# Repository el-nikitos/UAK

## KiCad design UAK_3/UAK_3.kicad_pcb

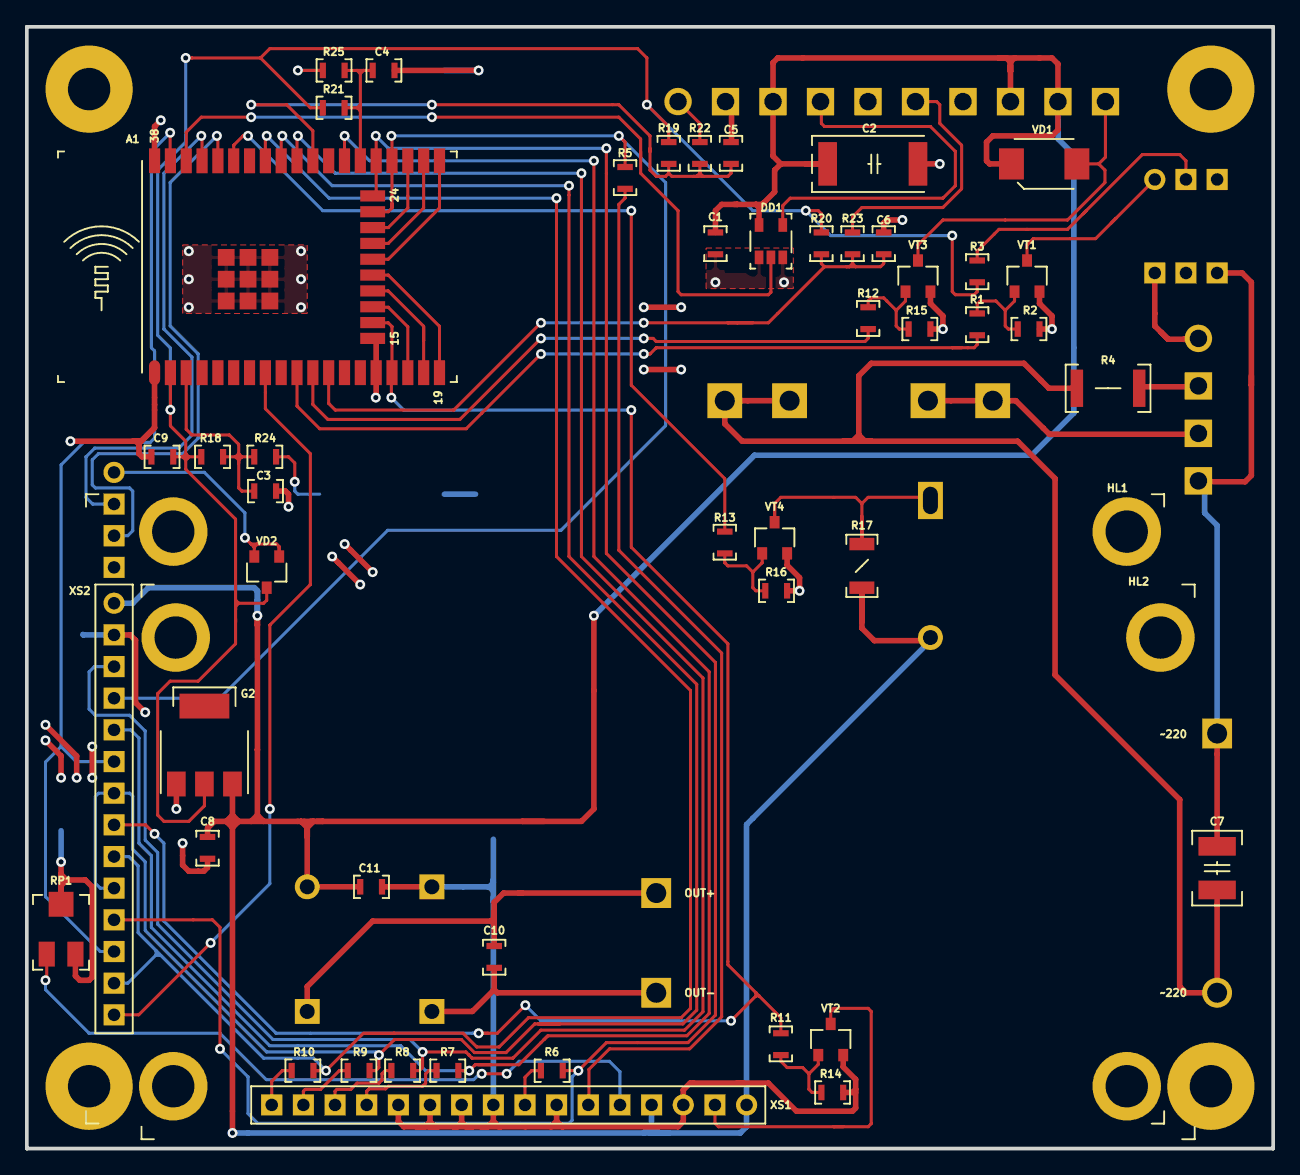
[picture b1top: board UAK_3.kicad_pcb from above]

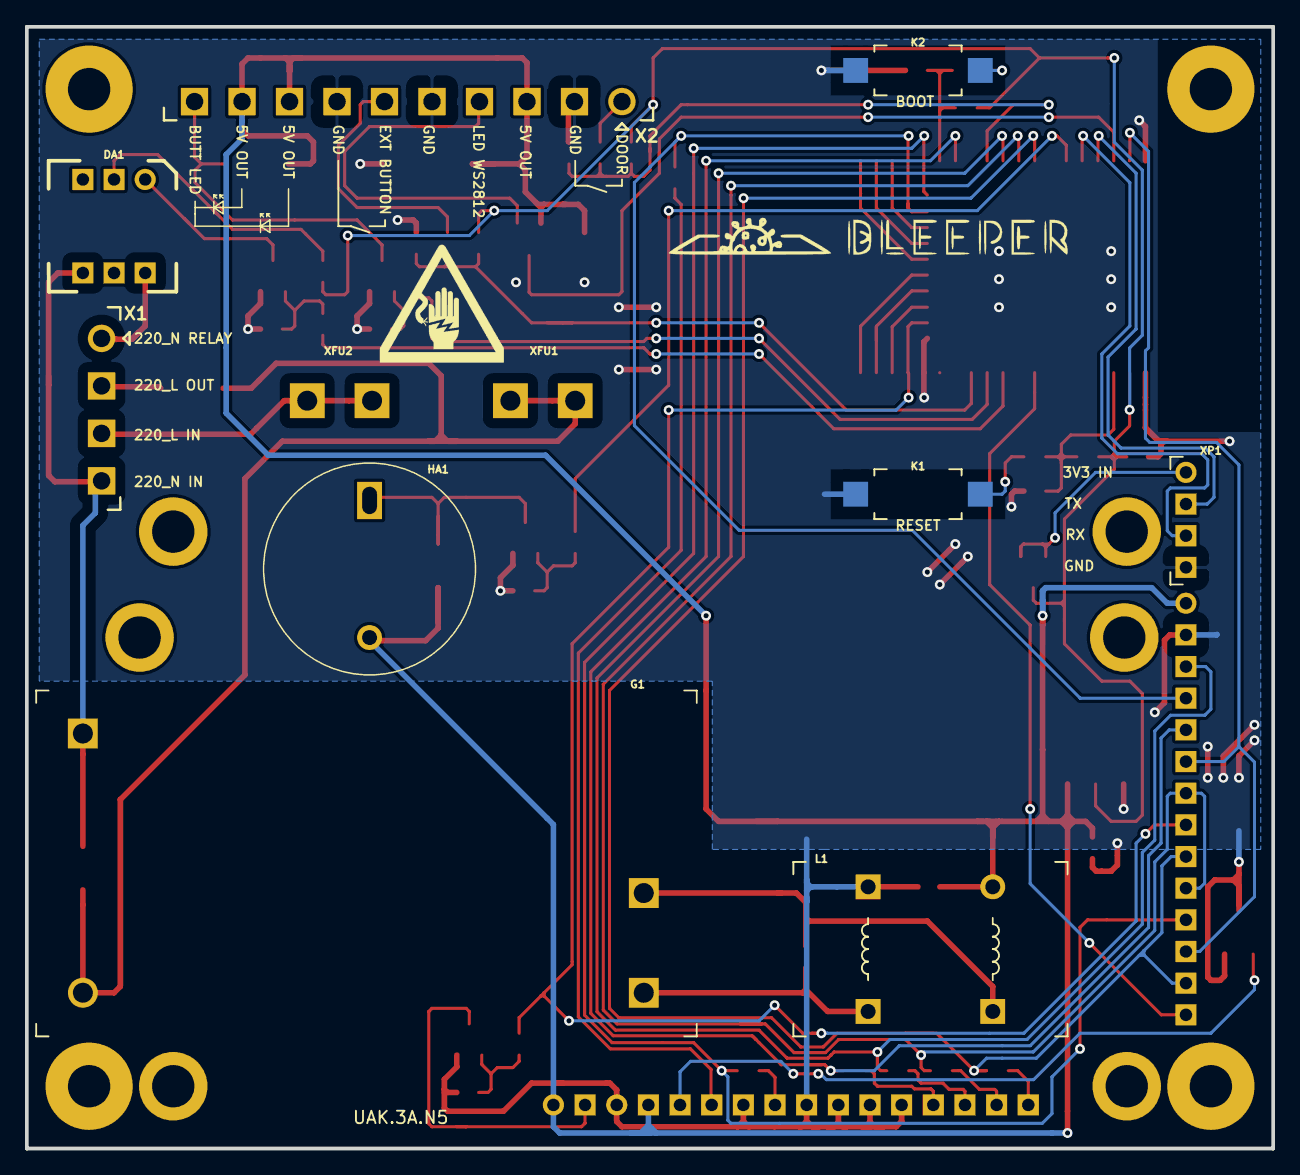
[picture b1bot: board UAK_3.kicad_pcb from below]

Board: 2 copper layers, 100.0 x 90.0 mm, 65 parts (13 on the bottom side), 51 nets.

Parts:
A1: модуль_esp32_wrover_OR_wroom32_SMD; ESP32_WROVER_or_WROOM32_pnp
C1, C3, C4, C5, C6, C8, C9, C10, C11: Конденсатор_керамический; Конденсатор_SMD_0603_pnp
C2: Конденсатор_К53-56А-32В-22_мкФ+-10проц.; Конденсатор_тантал_SMD_m7343_pnp
C7: Конденсатор_керамический; Конденсатор_SMD_1210_pnp
D1: LOGO; danger_220
D2: LOGO; bleeper_4x33
DA1: МОП-реле_КР293КП1Б; DIP6
DD1: Повторитель_M74VHC1GT125; SOT-23-5_pnp
G1: AC-DC-преобразователь_IRM-15-5; AC-DC_IRM-20-12
G2: стабилизатор_нерегулируемый_LM1117GS-3.3; Транзистор_NPN_SOT223_pnp
HA1: Излучатель_HPA17F; Зуммер_HPA17F
HL1: TFT-дисплей_ST7735_ILI9341; TFT_2.8_INCH
HL2: Жидкокристалический_индикатор_MT-16S2H-2KLW; ЖК_MT-16S2H_2DRL
K1, K2: Кнопка_FSMSM
L1: Дроссель_B82731-T2132-A20_2х6.8мГн_1.3А_250В; Дроссель_B82731
R1, R2, R3, R5, R6, R7, R8, R9, R10, R11, R12, R13, R14, R15, R16, R18, R19, R20, R21, R22, R23, R24, R25: Резистор_0,065Вт; Резистор_SMD_0603_0,065_Вт_pnp
R4: Резистор_0,5Вт; Резистор_SMD_2010-0,5_Вт_pnp
R17: Резистор_0,25Вт; Резистор_SMD_1206-0,25_Вт_pnp
RP1: Резистор_подстроечный_PVA3A103; резистор_подстроечный_3314J-1_pnp
VD1: Диод_шоттки_SK16; Диод_SMB_pnp
VD2: Набор_диодов_BAR43CFILM; Корпус_КТ-46_pnp
VT1, VT2, VT3, VT4: Транзистор_полевой_N-канальный_IRLML6344TR; Корпус_КТ-46_pnp
X1: Клеммник_х4; Клеммник_х4_шаг3,81_15EDGRC
X2: Клеммник_х10; Клеммник_х10_шаг3,81_15EDGRC
X3, X4, X5, X6: Крепежное_отверстие_М3; Крепежное_Отверстие_под_М3
XFU1, XFU2: Держатель_предохранителя_KLS5-266; Держатель_5х20
XP1: Вилка_WF-4R; Вилка_СНП389-4ВП32-1-1

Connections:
/3V3: A1.2, C9.1, G2.2, R3.2, R18.1, R19.1, R20.1, R21.1, VD2.3
/5V: C1.1, C2.1, C8.1, C11.1, DD1.5, G2.3, HA1.1, HL1.1, HL2.2, HL2.15, L1.1, R17.1, VD1.1, X2.3, X2.8, X2.9
/220_L: X1.3, XFU2.1
/220_L_FU: C7.1, G1.L, R4.1, XFU1.1
/220_L_OUT: R4.2, X1.2
/220_N: C7.2, DA1.4, G1.N, X1.4
/220_N_OUT: DA1.6, X1.1
/BOOT_SEL: A1.25, C4.1, R21.2, R25.2
/BOOT_UART_RX: A1.34, XP1.3
/BOOT_UART_TX: A1.35, XP1.2
/BUTT_1: R23.1, X2.6
/BUZZER: A1.33, R13.2
/DOOR_1: R22.1, X2.1
/DOOR_SENSOR: A1.28, C5.2, R19.2, R22.2
/D_OUT_1: VD1.2, VT3.3, X2.10
/EN_RESET: A1.3, C3.1, R18.2, R24.2
/EXT_BUTTON: A1.12, C6.2, R20.2, R23.2
/GND: A1.1, A1.15, A1.38, A1.39, C1.2, C2.2, C3.2, C4.2, C5.1, C6.1, C8.2, C9.2, C11.2, DD1.1, DD1.3, G2.1, HL1.2, HL2.1, HL2.5, HL2.7, HL2.8, HL2.9, HL2.10, K1.1, K2.1, L1.3, R2.2, R14.2, R15.2, R16.2, RP1.2, RP1.3, VT1.2, VT2.2, VT3.2, VT4.2, X2.2, X2.5, X2.7, XP1.4
/LCD_A0: A1.23, HL1.4, R5.2
/LCD_DATA_4: A1.26, HL1.5, R7.2
/LCD_DATA_5: A1.29, HL1.3, R8.2
/LCD_DATA_6: A1.30, HL1.7, HL1.10, R9.2
/LCD_DATA_7: A1.31, HL1.9, HL1.13, R10.2
/LCD_E: A1.24, HL1.11, R6.2
/LCD_LED: A1.16, HL1.8, R11.2
/LED_OUT: DD1.4, X2.4
/LED_WS2812: A1.36, DD1.2
/MC_220_OUT: A1.10, R1.2
/MC_OUT_1: A1.11, R12.2
/MOSI: A1.37, HL1.6, HL1.12
/SUPPLY_POWER/5V_NOISE: C10.1, G1.+V, L1.6
/TOUCH_IRQ: A1.8, HL1.14
unnamed: C10.2, G1.-V, L1.4
unnamed: DA1.1, VT1.3
unnamed: DA1.2, R3.1
unnamed: HA1.2, R17.2, VT4.3
unnamed: HL2.3, RP1.1
unnamed: HL2.4, R5.1
unnamed: HL2.6, R6.1
unnamed: HL2.11, R7.1
unnamed: HL2.12, R8.1
unnamed: HL2.13, R9.1
unnamed: HL2.14, R10.1
unnamed: HL2.16, VT2.3
unnamed: K1.2, R24.1
unnamed: K2.2, R25.1
unnamed: R1.1, R2.1, VT1.1
unnamed: R11.1, R14.1, VT2.1
unnamed: R12.1, R15.1, VT3.1
unnamed: R13.1, R16.1, VT4.1
unnamed: VD2.1, VD2.2, XP1.1

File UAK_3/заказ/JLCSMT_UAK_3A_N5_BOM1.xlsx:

Comment | Designator | Footprint | LCSC Part #（optional） |  | new name
ESP32-WROOM-32E | A1 | SMD38,18x25.5 | C701341 | 0 | ESP32-WROOM-32E
100nF 50V | C1 | 0603_C | C14663 | 0 | 100nF 50V
100uF 10V | C2 | CASE-D_7343 | C313070 | 0 | 100uF 10V
100nF 50V | C3 | 0603_C | C14663 | 0 | 100nF 50V
100nF 50V | C4 | 0603_C | C14663 | 1 | ?
100nF 50V | C5 | 0603_C | C14663 | 1 | ?
100nF 50V | C6 | 0603_C | C14663 | 1 | ?
22nF 1kV | C7 | 1210_C | C304015 | 0 | 22nF 1kV
10uF 10V | C8 | 0603_C | C19702 | 0 | 10uF 10V
10uF 10V | C9 | 0603_C | C19702 | 1 | ?
10uF 10V | C10 | 0603_C | C19702 | 1 | ?
10uF 10V | C11 | 0603_C | C19702 | 1 | ?
M74VHC1GT125DT1G | DD1 | SOT-23-5 | C457671 | 0 | M74VHC1GT125DT1G
SC1117-3.3V | G2 | SOT-223 | C173386 | 0 | SC1117-3.3V
240Ω | R1 | 0603_R | C101310 | 0 | 240Ω
10kΩ | R2 | 0603_R | C510290 | 0 | 10kΩ
150Ω | R3 | 0603_R | C336847 | 0 | 150Ω
130Ω | R4 | 2010_R | C406994 | 0 | 130Ω
240Ω | R5 | 0603_R | C101310 | 0 | 240Ω
240Ω | R6 | 0603_R | C101310 | 1 | ?
240Ω | R7 | 0603_R | C101310 | 1 | ?
240Ω | R8 | 0603_R | C101310 | 1 | ?
240Ω | R9 | 0603_R | C101310 | 1 | ?
240Ω | R10 | 0603_R | C101310 | 1 | ?
240Ω | R11 | 0603_R | C101310 | 1 | ?
240Ω | R12 | 0603_R | C101310 | 1 | ?
240Ω | R13 | 0603_R | C101310 | 1 | ?
10kΩ | R14 | 0603_R | C510290 | 0 | 10kΩ
10kΩ | R15 | 0603_R | C510290 | 1 | ?
10kΩ | R16 | 0603_R | C510290 | 1 | ?
1kΩ | R17 | 1206_R | C830401 | 0 | 1kΩ
10kΩ | R18 | 0603_R | C510290 | 0 | 10kΩ
10kΩ | R19 | 0603_R | C510290 | 1 | ?
10kΩ | R20 | 0603_R | C510290 | 1 | ?
10kΩ | R21 | 0603_R | C510290 | 1 | ?
240Ω | R22 | 0603_R | C101310 | 0 | 240Ω
240Ω | R23 | 0603_R | C101310 | 1 | ?
240Ω | R24 | 0603_R | C101310 | 1 | ?
240Ω | R25 | 0603_R | C101310 | 1 | ?
10K Variable Resistors | RP1 | 3314J | C36376 | 0 | 10K Variable Resistors
MDD SS24B | VD1 | SMB(DO-214AA) | C35501 | 0 | MDD SS24B
BAT54CLT1G | VD2 | SOT-23-3 | C14308 | 0 | BAT54CLT1G
IRLML6344TR | VT1 | SOT-23-3 | C693370 | 0 | IRLML6344TR
IRLML6344TR | VT2 | SOT-23-3 | C693370 | 1 | ?
IRLML6344TR | VT3 | SOT-23-3 | C693370 | 1 | ?
IRLML6344TR | VT4 | SOT-23-3 | C693370 | 1 | ?

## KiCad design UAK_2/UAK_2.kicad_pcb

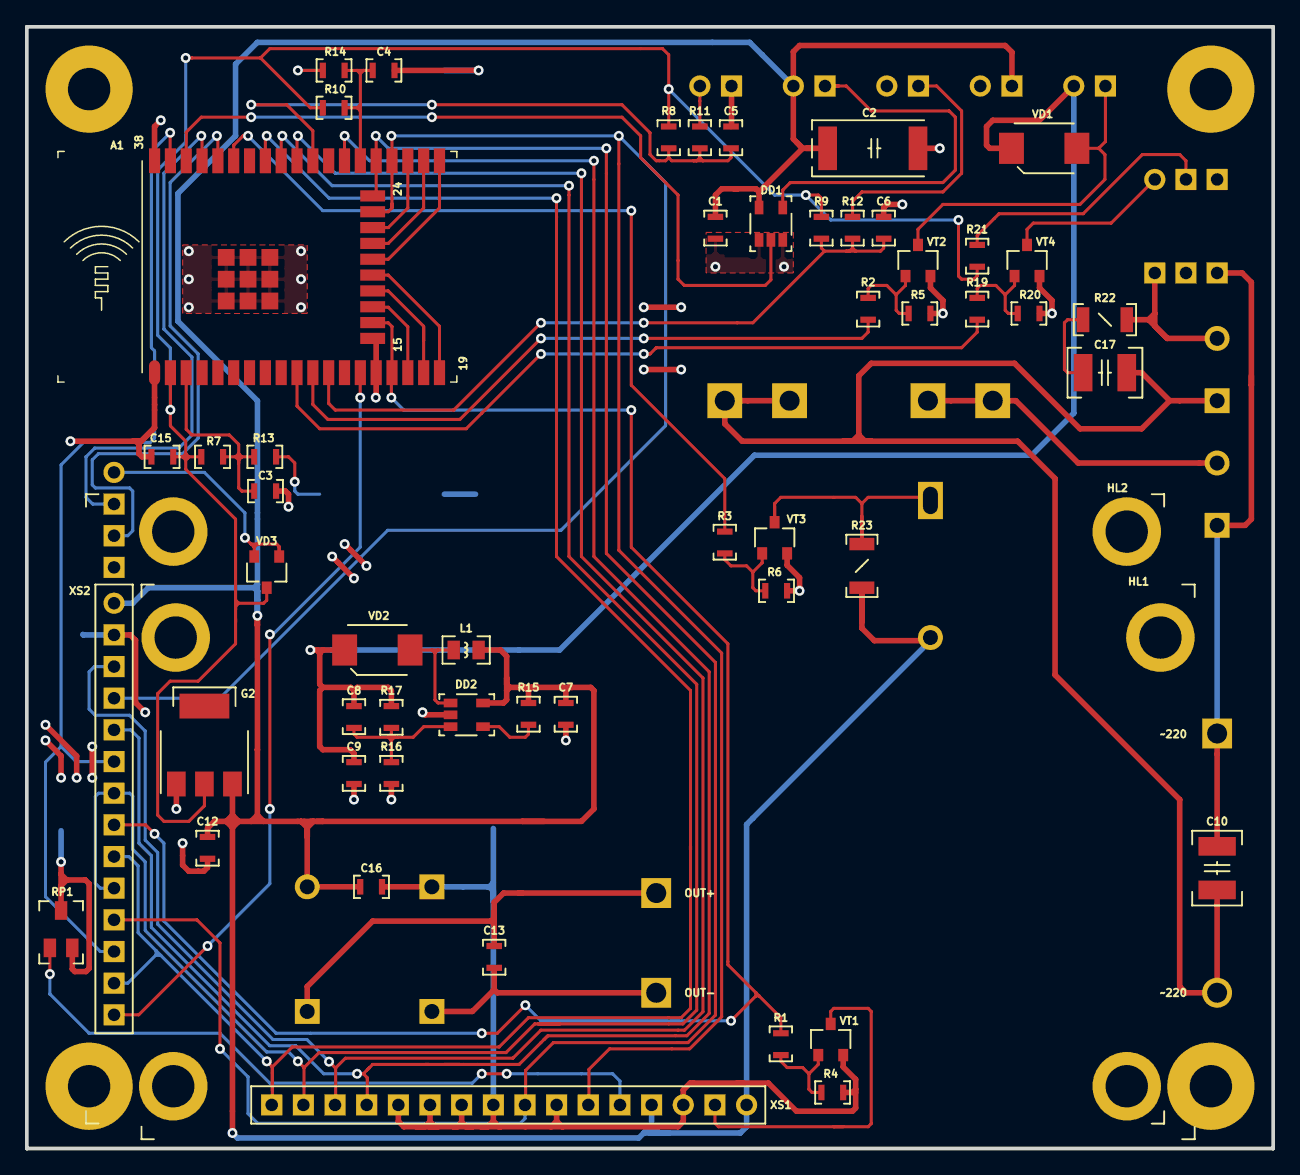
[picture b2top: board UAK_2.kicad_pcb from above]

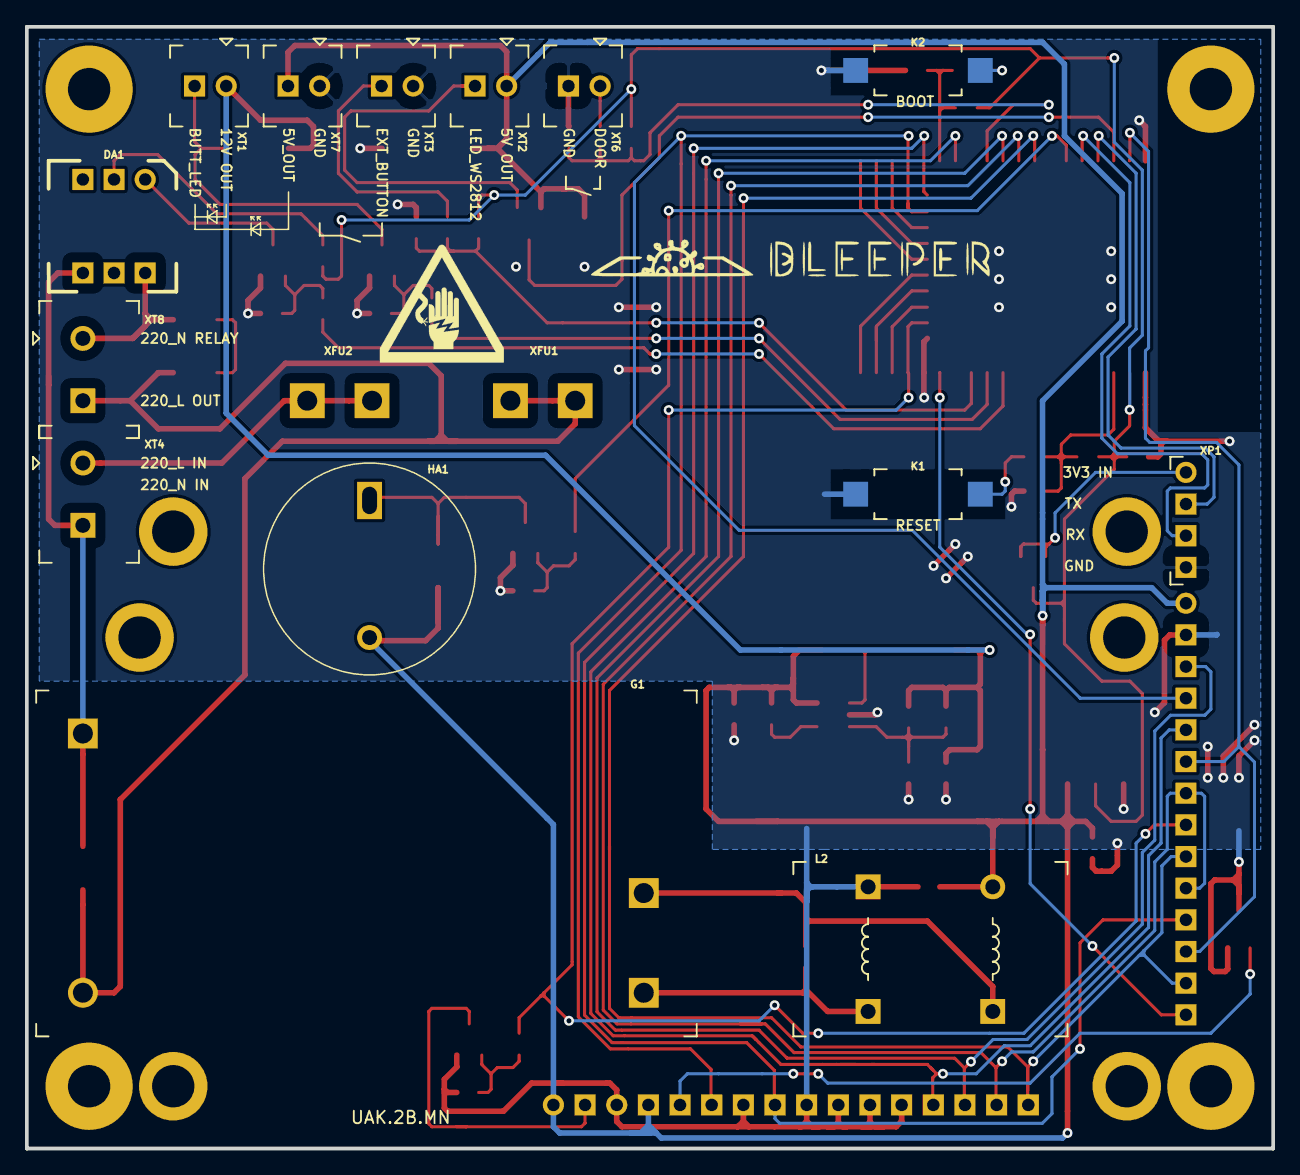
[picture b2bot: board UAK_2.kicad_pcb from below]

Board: 2 copper layers, 100.0 x 90.0 mm, 74 parts (18 on the bottom side), 49 nets.

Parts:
A1: модуль_esp32_wrover_OR_wroom32_SMD; ESP32_WROVER_or_WROOM32
C1, C3, C4, C5, C6, C7, C8, C9, C12, C13, C15, C16: Конденсатор_керамический; Конденсатор_SMD_0603
C2: Конденсатор_К53-56А-32В-22_мкФ+-10проц.; Конденсатор_тантал_SMD_m7343
C10, C17: Конденсатор_керамический; Конденсатор_SMD_1210
D1: LOGO; bleeper_4x33
D2: LOGO; danger_220
DA1: МОП-реле_КР293КП1Б; DIP6
DD1: Повторитель_M74VHC1GT125; Преобразователь_LM2703_SOT-23-5
DD2: Микросхема_DCDC_step_UP_LM2703; Преобразователь_LM2703_SOT-23-5
G1: AC-DC-преобразователь_IRM-15-5; AC-DC_IRM-20-12
G2: стабилизатор_нерегулируемый_LM1117GS-3.3; Транзистор_NPN_SOT223
HA1: Излучатель_HPA17F; Зуммер_HPA17F
HL1: Жидкокристалический_индикатор_MT-16S2H-2KLW; ЖК_MT-16S2H_2DRL
HL2: TFT-дисплей_ST7735_ILI9341; TFT_2.8_INCH
K1, K2: Кнопка_FSMSM
L1: Чип-индуктивность_10мкГн_0.2А_20проц.; Чип-индуктивность_SMD_0805
L2: Дроссель_B82731-T2132-A20_2х6.8мГн_1.3А_250В; Дроссель_B82731
R1, R2, R3, R4, R5, R6, R7, R8, R9, R10, R11, R12, R13, R14, R15, R16, R17, R19, R20, R21: Резистор_0,065Вт; Резистор_SMD_0603_0,065_Вт
R22, R23: Резистор_0,25Вт; Резистор_SMD_1206-0,25_Вт
RP1: Резистор_подстроечный_PVA3A103; резистор_подстроечный_PVZ3A334
VD1, VD2: Диод_шоттки_SK16; Диод_SMB
VD3: Набор_диодов_BAR43CFILM; Корпус_КТ-46
VT1, VT2, VT3, VT4: Транзистор_полевой_N-канальный_IRLML6344TR; Корпус_КТ-46
X1, X2, X3, X4: Крепежное_отверстие_М3; Крепежное_Отверстие_под_М3
XFU1, XFU2: Держатель_предохранителя_KLS5-266; Держатель_5х20
XP1: Вилка_WF-4R; Вилка_СНП389-4ВП32-1-1
XT1, XT2, XT3, XT6, XT7: Клеммник_х2_308-021-14; Клеммник_х2_шаг2.54
XT4, XT8: Клеммник_х2_KLS2-300-5.00-02P-2S; Клеммник_х2_шаг5

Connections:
/3V3: A1.2, C15.1, G2.2, R7.1, R8.1, R9.1, R10.1, R21.2, VD3.3
/5V: C1.1, C2.1, C7.1, C12.1, C16.1, DD1.5, DD2.5, G2.3, HA1.1, HL1.2, HL1.15, HL2.1, L1.2, L2.1, R15.1, R23.1, XT2.1, XT7.2
/12V: C8.2, C9.1, R17.1, VD1.2, VD2.2, XT1.1
/220_L: XFU2.1, XT4.1
/220_L_FU: C10.1, C17.2, G1.L, XFU1.1, XT8.2
/220_N: C10.2, DA1.4, G1.N, XT4.2
/220_N_OUT: DA1.6, R22.1, XT8.1
/BOOT_SEL: A1.25, C4.1, R10.2, R14.2
/BOOT_UART_RX: A1.34, XP1.3
/BOOT_UART_TX: A1.35, XP1.2
/BUTT_1: R12.1, XT3.2
/BUZZER: A1.33, R3.2
/DOOR_1: R11.1, XT6.1
/DOOR_SENSOR: A1.28, C5.2, R8.2, R11.2
/D_OUT_1: VD1.1, VT2.3, XT1.2
/EN_RESET: A1.3, C3.1, R7.2, R13.2
/EXT_BUTTON: A1.12, C6.2, R9.2, R12.2
/GND: A1.1, A1.15, A1.38, A1.39, C1.2, C2.2, C3.2, C4.2, C5.1, C6.1, C7.2, C9.2, C12.2, C15.2, C16.2, DD1.1, DD1.3, DD2.2, G2.1, HL1.1, HL1.5, HL1.7, HL1.8, HL1.9, HL1.10, HL2.2, K1.1, K2.1, L2.3, R4.2, R5.2, R6.2, R16.2, R20.2, RP1.2, RP1.3, VT1.2, VT2.2, VT3.2, VT4.2, XP1.4, XT3.1, XT6.2, XT7.1
/LCD_A0: A1.23, HL1.4, HL2.4
/LCD_DATA_4: A1.26, HL1.11, HL2.5
/LCD_DATA_5: A1.29, HL1.12, HL2.3
/LCD_DATA_6: A1.30, HL1.13, HL2.7, HL2.10
/LCD_DATA_7: A1.31, HL1.14, HL2.9, HL2.13
/LCD_E: A1.24, HL1.6, HL2.11
/LCD_LED: A1.16, HL2.8, R1.2
/LED_OUT: DD1.4, XT2.2
/LED_WS2812: A1.36, DD1.2
/MC_220_OUT: A1.10, R19.2
/MC_OUT_1: A1.11, R2.2
/MOSI: A1.37, HL2.6, HL2.12
/SUPPLY_POWER/5V_NOISE: C13.1, G1.+V, L2.6
/TOUCH_IRQ: A1.14, HL2.14
unnamed: C8.1, DD2.3, R16.1, R17.2
unnamed: C13.2, G1.-V, L2.4
unnamed: C17.1, R22.2
unnamed: DA1.1, VT4.3
unnamed: DA1.2, R21.1
unnamed: DD2.1, L1.1, VD2.1
unnamed: DD2.4, R15.2
unnamed: HA1.2, R23.2, VT3.3
unnamed: HL1.3, RP1.1
unnamed: HL1.16, VT1.3
unnamed: K1.2, R13.1
unnamed: K2.2, R14.1
unnamed: R1.1, R4.1, VT1.1
unnamed: R2.1, R5.1, VT2.1
unnamed: R3.1, R6.1, VT3.1
unnamed: R19.1, R20.1, VT4.1
unnamed: VD3.1, VD3.2, XP1.1

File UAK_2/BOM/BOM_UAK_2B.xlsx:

Позиционное обозначение | Ссылка для справки | Наименование | Кол-во | Сторона установки | Метод установки | кол-во на 50+10%
A1 | https://www.terraelectronica.ru/product/2292549 | ESP32-WROOM-32 [4MB] | 1 | лицевая | поверхностный | 55.000000000000007
C2 | https://www.terraelectronica.ru/product/363479 | Конденсатор D 100 мкФ 10В 20% | 1 | лицевая | поверхностный | 55.000000000000007
> C1, C3-C6 | https://www.terraelectronica.ru/product/1044009 | Конденсатор 0603 100 нФ 50В 5% | 5 | лицевая | поверхностный | 262.5
C8 | https://www.terraelectronica.ru/product/664080 | Конденсатор 0603 220 пФ 50В 5% | 1 | лицевая | поверхностный | 55.000000000000007
> C7, C9, C12, C13, C15, C16 | https://www.terraelectronica.ru/product/1489875 | Конденсатор 0603 10 мкФ 25В 20% | 6 | лицевая | поверхностный | 315
> C10, C17 | https://www.chipdip.ru/product/grm32qr72j223k | Конденсатор 1210 0,022 мкФ 630В 10% | 2 | лицевая | поверхностный | 110.00000000000001
DA1 | https://www.chipdip.ru/product/kr293kp1b | МОП-реле КР293КП1Б | 1 | обратная | в панель DA1* | 55.000000000000007
DA1* | https://www.chipdip.ru/product/trs-6 | DIP-панель | 1 | обратная | выводной | 55.000000000000007
DD1 | https://www.terraelectronica.ru/product/287011 | Повторитель M74VHC1GT125DT1G | 1 | лицевая | поверхностный | 55.000000000000007
DD2 | https://www.terraelectronica.ru/product/287900 | DC-DC LM27313XMF/NOPB | 1 | лицевая | поверхностный | 55.000000000000007
G1 | https://www.chipdip.ru/product/irm-15-5 | AC-DC IRM-15-5 | 1 | обратная | выводной | 55.000000000000007
G2 | https://www.chipdip.ru/product/lm1117gs-3.3 | LDO LM1117GS-3.3 | 1 | лицевая | поверхностный | 55.000000000000007
HA1 | https://www.chipdip.ru/product/hpa17f | Зуммер HPA17F | 1 | обратная | выводной | 55.000000000000007
> K1, K2 | https://www.terraelectronica.ru/product/1087727 | Кнопка FSMSM | 2 | обратная | поверхностный | 110.00000000000001
L1 | https://www.chipdip.ru/product/mlz2012m100ht000-10 | Чип-индуктивность 0805 10 мкГн 0,2А 20% | 1 | лицевая | поверхностный | 55.000000000000007
L2 | https://www.chipdip.ru/product/b82731-t2132-a20 | Дроссель B82731-T2132-A20 | 1 | обратная | выводной | 55.000000000000007
> R4-R10, R15, R16, R20 | https://www.terraelectronica.ru/product/562124 | Резистор 0603 10 кОм 5% | 10 | лицевая | поверхностный | 550
> R1-R3, R11-R14, R19 | https://www.terraelectronica.ru/product/559067 | Резистор 0603 240 Ом 5% | 8 | лицевая | поверхностный | 440.00000000000006
R17 | https://www.terraelectronica.ru/product/2782214 | Резистор 0603 82 кОм 5% | 1 | лицевая | поверхностный | 55.000000000000007
R21 | https://www.terraelectronica.ru/product/569439 | Резистор 0603 150 Ом 5% | 1 | лицевая | поверхностный | 55.000000000000007
> R22, R23 | https://www.terraelectronica.ru/product/2782734 | Резистор 1206 4,7 кОм 5% | 2 | лицевая | поверхностный | 110.00000000000001
RP1 | https://www.chipdip.ru/product/3303x-3-503 | Резистор подстроечный 50 кОм | 1 | лицевая | поверхностный | 55.000000000000007
> VD1, VD2 | https://www.terraelectronica.ru/product/129173 | Диод шоттки SK16 (1А 60В) | 2 | лицевая | поверхностный | 110.00000000000001
VD3 | https://www.terraelectronica.ru/product/296487 | Набор диодов BAR43CFILM | 1 | лицевая | поверхностный | 55.000000000000007
> VT1-VT4 | https://www.chipdip.ru/product/irlml6344trpbf | Транзистор N-канал IRLML6344TRPBF | 4 | лицевая | поверхностный | 220.00000000000003
> XFU1, XFU2 | https://www.chipdip.ru/product/kls5-266-fh-100 | Держатель KLS5-266 | 2 | обратная | выводной | 110.00000000000001
XP1 | https://www.chipdip.ru/product/wf-4r | Вилка угловая WF-4R | 1 | обратная | выводной | 55.000000000000007
XS1 | https://www.chipdip.ru/product/pbs16 | Розетка PBS-16 | 1 | лицевая | выводной | 55.000000000000007
XS2 | https://www.chipdip.ru/product/pbs-14 | Розетка PBS-14 | 1 | лицевая | выводной
> XT4, XT8 | https://www.chipdip.ru/product/kls2-300-5.00-02p-2s-dg300-5.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 | Клеммник KLS2-300-5.00-02P-2S (шаг 5 мм) | 2 | обратная | выводной | 110.00000000000001
> XT1-XT3, XT6, XT7 | https://www.chipdip.ru/product/308-021-12-14 | Клеммник 308-021-14 (шаг 2,54 мм) | 5 | обратная | выводной | 262.5

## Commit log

2020-08-06 Процессорный модуль с USB и выходами типа открытый сток
2020-09-05 Процессорный модуль ESP32
2020-09-05 начата схема, есть лист питания
2020-09-06 BOOT&PRG, концевик, ЖК, звук, подсветка - без трассировки
2020-09-06 нет коммутации 220В, остальная схема есть, нет трассировка
2020-09-06 подготовлена схема, нет трассировки
2020-09-06 подготовлена схема UAK_0A
2020-09-06 есть трассировка питания
2020-09-07 начата установка ESP32
2020-09-07 закончена трассировка, обновлена PDF и PNG, добавлен STEP
2020-09-08 UAK_0C. Убрал лого Ni, добавлены gerber
2020-09-19 правки атрибутов УГО, заменен резистор RC-фильтра
2020-09-19 добавлена прошивка в arduino ide для проверки функционирования
2020-09-19 UAK.1A.M9
    исправлено межоснвое растояние крепежки экрана, заменен диод закольцовки зумера на сопротивление 4,7 кОм
2020-09-22 ссылка на сайт заменена на лого
2020-09-23 исправлено лого bleeper, исправлено место зуммера
2020-09-23 начата подготовка ТО, начат проект вер.1
2020-09-25 1B: заменены предохранители,обновлено питание,не добавлен второй дисплей
2020-09-25 обновлен перечень элементов
2020-09-26 UAK.1C.M9, подготовлены gerber, схема, BOM
    обновлена маркировка, заполнен BOM
2020-09-28 рыба заявки в м-плата
2020-09-29 добавлена схема элементов для монтажа ревизии 0C
2020-10-03 обновлены 3D в проекте и step
2020-10-03 ПЭ и СБ на UAK.1C
2020-10-03 подготавливается wiki_документ и сопутствующие файлы
2020-10-17 исправлен номинал преда. в wiki, добавлена 3D кожуха преда.
2020-10-18 тестовая прошивка uab-1c, рыба прошивки TFT, документ с зав/ном
2020-11-01 обновлены зав.ном, прошивка TFT_test заливает экран, UAK_2 init
2020-11-04 добавлена методика программирования, на схему вынесен новый дисплей
2020-11-04 крышка предохранителя
2020-11-04 UAK.2A.MN + PDF +STEP
2020-11-07 заменен буфер, перекинуты ножки контроллера,, обновлены PCB +STEP +PDF
2020-11-07 UAK_2B: GERBER +СБ +ПЭ
    исправлено посадочное зуммера, подготовлена документация
2020-11-08 добавлены исполнения в СБ
2020-11-14 по замечанию резонита нанесена маркировка в СБ
2020-12-05 в тестовой прошиве ревизии UAK_2 проверка стала двухстрочной
2021-01-17 #define TOUCH_IRQ 32
2021-02-06 компилирующаяся прошивка
2021-02-22 в тестовой прошивке добавлена подтяжка pull-down
2021-04-24 убран DC/DC 5/12В, перекинут канал прерывания TFT
2021-04-24 добавлены сопротивления: в управление ЖК и выход 220
2021-04-25 заменены клеммники
2021-04-25 заменен потенциометр, начал формировать BOM
2021-05-08 BOM переопределен по всему, кроме резисторов
2021-05-08 подготовлены файлы для заказа в JLCPCB
2021-05-09 BOM и CPL поправлены под китай, убрана мира слоев
